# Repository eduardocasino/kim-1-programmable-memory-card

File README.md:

# KIM-1 Programmable Memory Board for the MTU Backplane

## **WARNINGS**

**THIS IS A WORK IN PROGRESS AND MAY CONTAIN ERRORS. USE AT YOUR OWN RISK!!!**

**Make sure to configure composite video output when connecting a composite monitor, and VGA output when using a VGA monitor. The video data and HSYNC pins are shared between both connectors, and if not properly configured, the signal MAY DAMAGE your monitor — especially older models.**

## About

This is a fully programmable RAM/ROM expansion board for the KIM-1. Two hardware versions are available which use exactly the same firmware and tools:

* One for MTU backplanes, like the one in the original K-1005 card file, my [expansion card](https://github.com/eduardocasino/kim-1-mtu-expansion-card) or my [buffered motherboard](https://github.com/eduardocasino/kim-1-mtu-motherboard).
* One for the [PAL-2](https://www.tindie.com/products/kim1/pal-2-a-mos-6502-powered-computer-kit/), a KIM-1 clone by Liu GN. **IMPORTANT: Read the hardware specific notes for the PAL-2**.

There is also [an adapter](https://github.com/eduardocasino/kim-1-programmable-memory-card/tree/main/hardware/pal-2-kim-adapter) for connecting the PAL-2 version directly to the KIM-1 expansion connector. This is the best option if you don't have/need/want an MTU backplane.

It uses a Raspberry Pi Pico W to emulate the 64K RAM/ROM memory map, and has some cool features:

* Can emulate RAM and/or ROM at any address of the KIM-1 memory map and with byte granularity so you can individually enable, disable, mark as RW or RO each and every byte of the 64K address space. It can also take over the KIM-1 system RAM and ROM, so it can be used as a diagnostic tool or to relive a KIM-1 with dead RAM.
* A default memory map and data are stored in the Pico flash memory and it is available at boot time.
* Runs a configuration web server with a RESTish API so you can configure and read or write all or any part of memory contents over Wifi and on the fly.
* The board is powered by the KIM-1, but it can also be dual powered by the KIM-1 and the USB port. This is useful, for example, if you are developing a boot ROM: you can power off the KIM, modify the boot program over wifi and turn it on again to test your changes.
* It emulates an [MTU K-1008 Visable Memory Card](https://github.com/eduardocasino/k-1008-visable-memory-card-replica). It can be mapped to the same addresses as the real one (and change that mapping while running) and gives configurable composite NTSC or PAL output through the RCA connector or VGA output through the DB-15 one. Simultaneous composite and VGA output is not possible.
* Emulates an [K-1013 floppy disk controller](http://retro.hansotten.nl/uploads/mtu/MTU%20K-1013%20manual.pdf) with up to four disks, reading and writing to disk images into the SD card (Still in beta)

A config utility, memcfg, is provided to setup the board and facilitate the communication with the REST API. This is an overview of its functionality. Please see the [README.md file](https://github.com/eduardocasino/kim-1-programmable-memory-card/tree/main/tools) for detailed usage instructions:

* Generate configuration files ready to be flashed into the Pico: WiFi parameters, video format and default memory map and contents.
* Get or modify the memory map.
* Read memory contents and generate output in different formats: hexdump, Intel hex, binary, prg and raw. The raw format is how the Pico stores the memory map. Each memory address contains a 16 bit integer. The least significant byte is the content and the most significant one is a bitmap that indicates if the memory is enabled or disabled and writeable or read-only.
* Write memory contents from file or command line. The file formats supported are Intel hex, binary, prg and raw. Also, binary and raw data can be specified as a string from the command line.
* Modify the base address for the K-1008 emulation
* Manages disk images

### [KIM-1 version](https://github.com/eduardocasino/kim-1-programmable-memory-card/tree/main/hardware/kim-1-mtu)
### [PAL-2 version](https://github.com/eduardocasino/kim-1-programmable-memory-card/tree/main/hardware/pal-2)
### [KIM-1 adapter for the PAL-2 version](https://github.com/eduardocasino/kim-1-programmable-memory-card/tree/main/hardware/pal-2-kim-adapter)
### [Firmware](https://github.com/eduardocasino/kim-1-programmable-memory-card/tree/main/firmware)
### [Tools (memcfg)](https://github.com/eduardocasino/kim-1-programmable-memory-card/tree/main/tools)

***NOTE***: This is a picture of a KIM-1 version prototype. The bodges are not needed in the current design.

## Licensing

This is a personal project that I am sharing in case it is of interest to any retrocomputing enthusiast and all the information in this repository is provided "as is", without warranty of any kind. I am not liable for any damages that may occur, whether it be to individuals, objects, KIM-1 computers, kittens or any other pets. **It should also be noted that everything in this repository is a work in progress, may have not been thoroughly tested and may contain errors, therefore anyone who chooses to use it does so at their own risk**.

This work is licensed under a [Creative Commons Attribution-ShareAlike 4.0 International License](http://creativecommons.org/licenses/by-sa/4.0/).

See the LICENSE.md file for details.

## Acknowledgements

* Richard Hulme for his [PicoROM implementation](https://github.com/rhulme/picoROM_pio).
* Jan Cumps on [how to reserve a flash memory block for persistent storage](https://community.element14.com/products/raspberry-pi/b/blog/posts/raspberry-pico-c-sdk-reserve-a-flash-memory-block-for-persistent-storage).
* Jeremy P Bentham for his [PicoWi library](http://iosoft.blog/picowi)
* Alan Reed for his [composite video output implementation](https://github.com/alanpreed/pico-composite-video).
* Hunter Adams for his [VGA implementation](https://github.com/vha3/Hunter-Adams-RP2040-Demos)
* Luciano Veronese for the BOM and component placement files for the KIM-1 version.

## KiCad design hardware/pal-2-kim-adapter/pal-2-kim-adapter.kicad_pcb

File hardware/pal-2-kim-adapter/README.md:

# PAL-2 version to KIM-1 adapter

## DECEN signal

As well as for the PAL, the DECEN pin must be connected to pin K in the Application connector. You can do this using a clip probe.

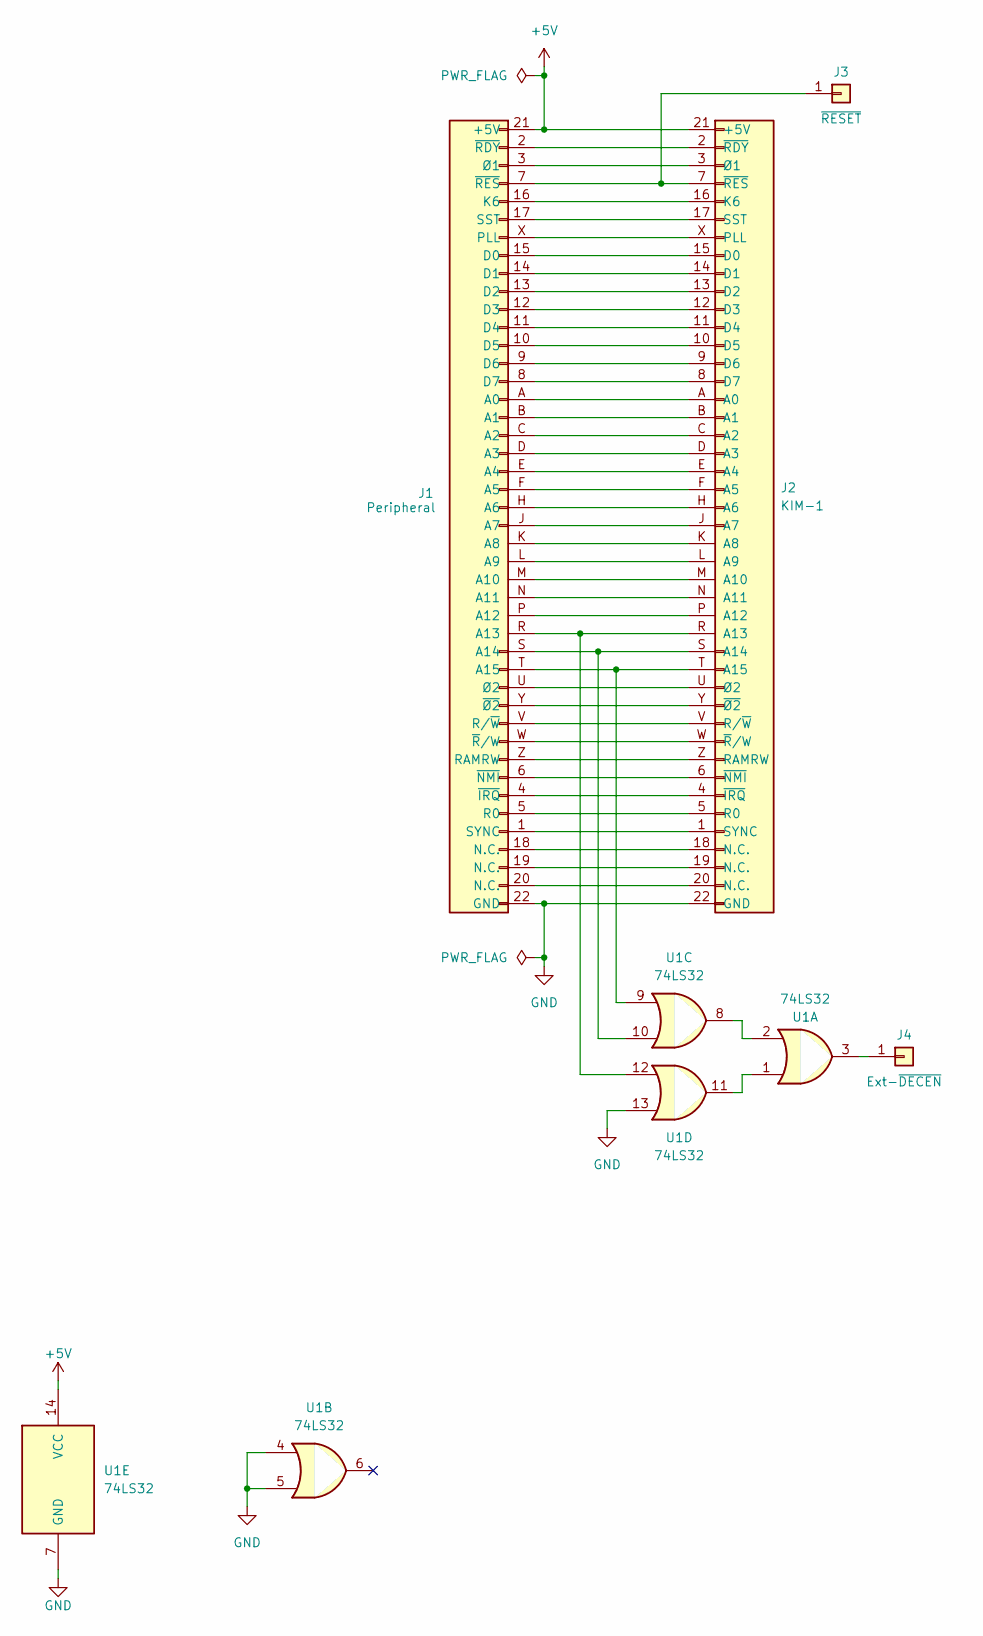
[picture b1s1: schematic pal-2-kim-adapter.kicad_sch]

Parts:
J1: Peripheral; PinSocket_2x22_P2.54mm_Horizontal
J2: KIM-1; KIM_EDGE
J3: ~{RESET}; PinHeader_1x01_P2.54mm_Horizontal
J4: Ext-~{DECEN}; PinHeader_1x01_P2.54mm_Vertical
U1: 74LS32; DIP-14_W7.62mm

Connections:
+5V: J1.21 (+5V), J2.21 (+5V), U1.14 (VCC)
GND: J1.22 (GND), J2.22 (GND), U1.4, U1.5, U1.7 (GND), U1.13
unnamed: J1.A (A0), J2.A (A0)
unnamed: J1.B (A1), J2.B (A1)
unnamed: J1.C (A2), J2.C (A2)
unnamed: J1.D (A3), J2.D (A3)
unnamed: J1.E (A4), J2.E (A4)
unnamed: J1.F (A5), J2.F (A5)
unnamed: J1.H (A6), J2.H (A6)
unnamed: J1.J (A7), J2.J (A7)
unnamed: J1.K (A8), J2.K (A8)
unnamed: J1.L (A9), J2.L (A9)
unnamed: J1.M (A10), J2.M (A10)
unnamed: J1.N (A11), J2.N (A11)
unnamed: J1.P (A12), J2.P (A12)
unnamed: J1.R (A13), J2.R (A13), U1.12
unnamed: J1.S (A14), J2.S (A14), U1.10
unnamed: J1.T (A15), J2.T (A15), U1.9
unnamed: J1.15 (D0), J2.15 (D0)
unnamed: J1.14 (D1), J2.14 (D1)
unnamed: J1.13 (D2), J2.13 (D2)
unnamed: J1.12 (D3), J2.12 (D3)
unnamed: J1.11 (D4), J2.11 (D4)
unnamed: J1.10 (D5), J2.10 (D5)
unnamed: J1.9 (D6), J2.9 (D6)
unnamed: J1.8 (D7), J2.8 (D7)
unnamed: J1.16 (K6), J2.16 (K6)
unnamed: J1.18 (N.C.), J2.18 (N.C.)
unnamed: J1.19 (N.C.), J2.19 (N.C.)
unnamed: J1.20 (N.C.), J2.20 (N.C.)
unnamed: J1.X (PLL), J2.X (PLL)
unnamed: J1.5 (R0), J2.5 (R0)
unnamed: J1.Z (RAMRW), J2.Z (RAMRW)
unnamed: J1.V (R/~W), J2.V (R/~W)
unnamed: J1.17 (SST), J2.17 (SST)
unnamed: J1.1 (SYNC), J2.1 (SYNC)
unnamed: J1.4 (~IRQ), J2.4 (~IRQ)
unnamed: J1.6 (~NMI), J2.6 (~NMI)
unnamed: J1.2 (~RDY), J2.2 (~RDY)
unnamed: J1.7 (~RES), J2.7 (~RES), J3.1
unnamed: J1.W (~R/W), J2.W (~R/W)
unnamed: J1.Y (~Ø2), J2.Y (~Ø2)
unnamed: J1.3 (Ø1), J2.3 (Ø1)
unnamed: J1.U (Ø2), J2.U (Ø2)
unnamed: J4.1, U1.3
unnamed: U1.1, U1.11
unnamed: U1.2, U1.8

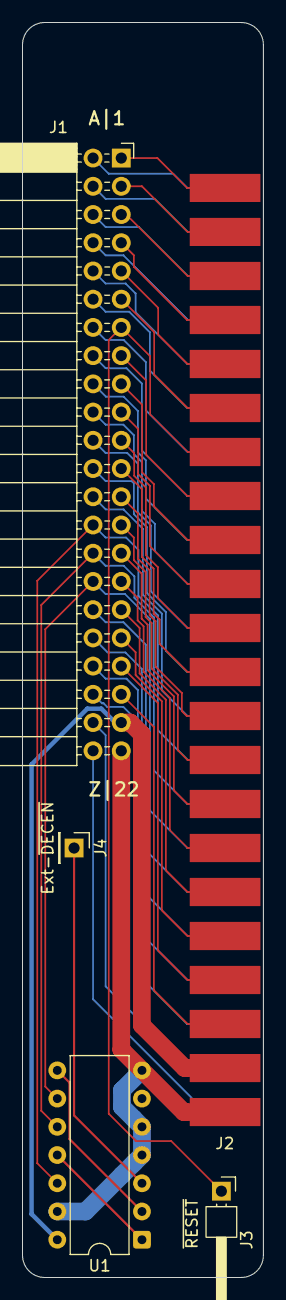
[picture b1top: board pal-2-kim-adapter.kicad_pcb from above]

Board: 2 copper layers, 21.7 x 112.9 mm, 5 parts (0 on the bottom side), 47 nets.

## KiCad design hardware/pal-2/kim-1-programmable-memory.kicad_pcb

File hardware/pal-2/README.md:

# Notes for the PAL-2 version

## DECEN signal

The DECEN pin must be connected to pin K in the Application connector. You can do this using a clip probe as shown in the picture below:

## PAL-2 mod

### **WARNING**

**THIS MOD MAY DAMAGE YOUR PAL-2 IF PERFORMED INCORRECTLY. DO IT AT YOUR OWN RISK!!!**

The PAL-2 behaves differently from the KIM-1 when the #DECEN signal goes high.

On the KIM-1, this signal disables all internal address decoding, allowing an expansion card to take over. However, on the PAL-2, the signal is wire-ORed with the 8K0 enable output of the first decoder, so it effectively has no impact.

To enable expansion card functionality, a simple modification must be performed on the PAL-2:

* Cut the trace that connects pin K of the Application connector to pin 12 of U6, and the trace connecting pin 12 of U8 to ground.
* Solder a wire from pin K of the Application connector to pin 12 of U8.
* Solder a 3.9kΩ resistor from pin 12 of U8 to any ground point on the board.

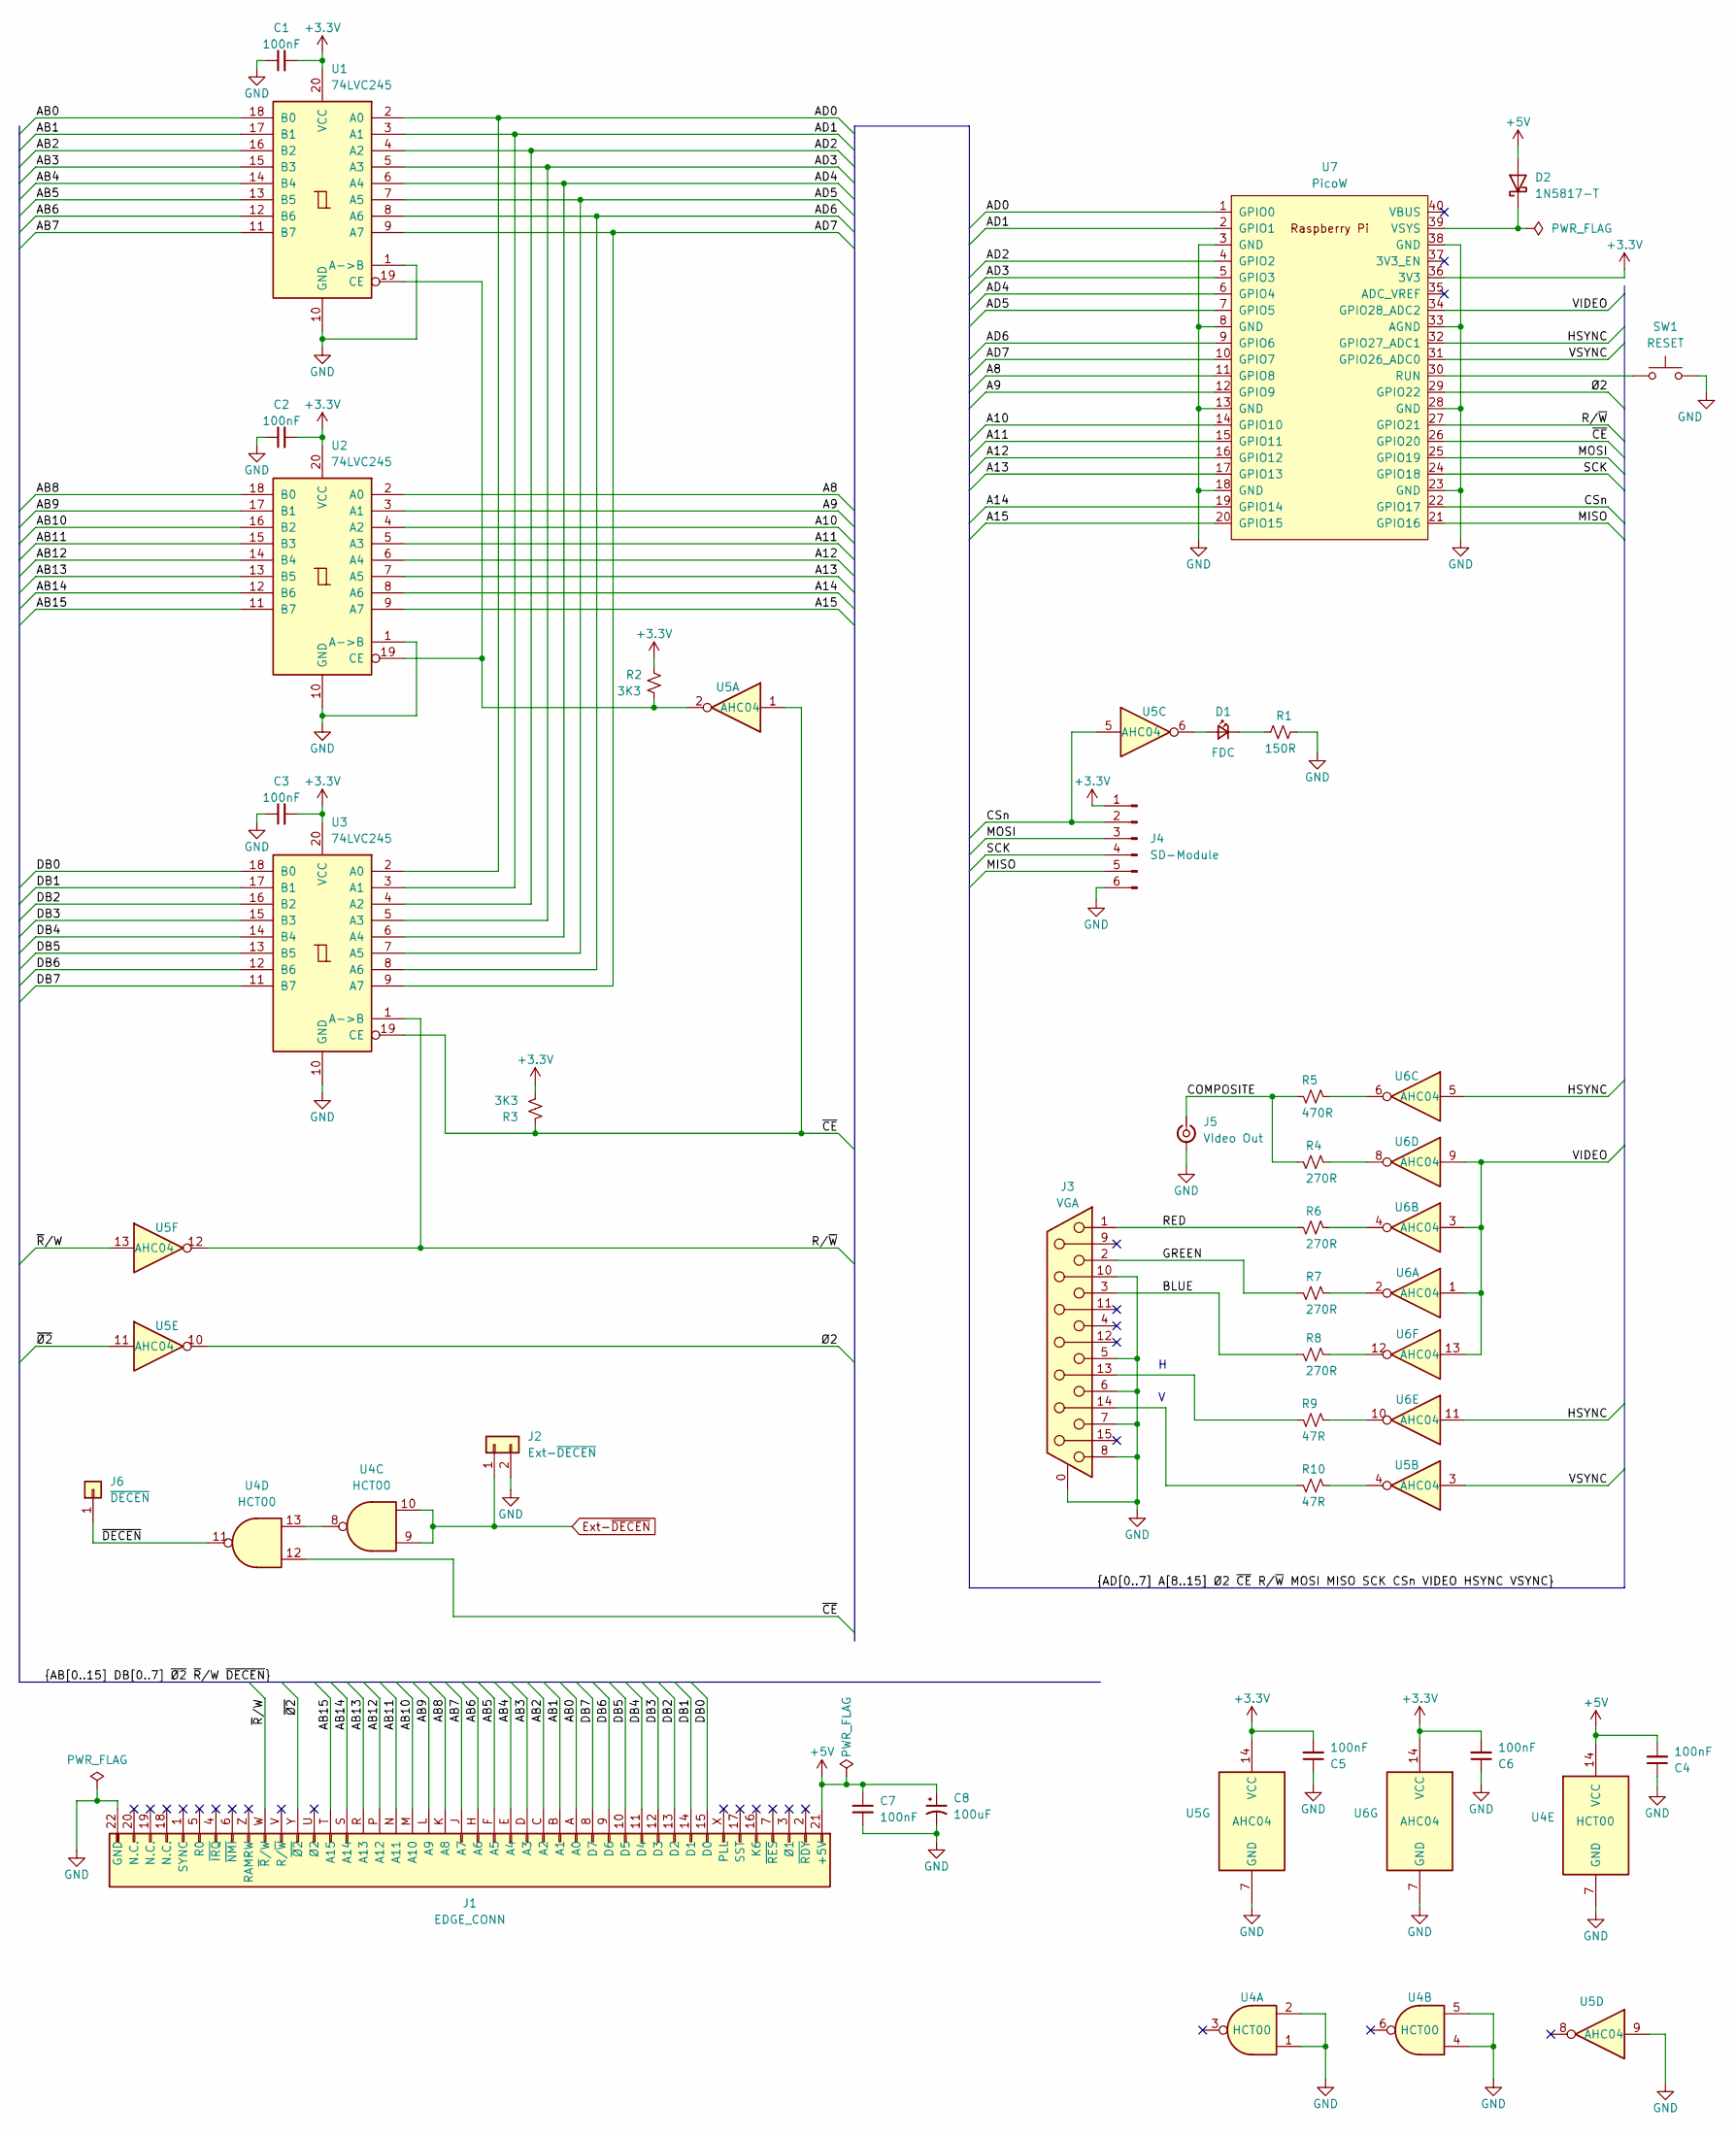
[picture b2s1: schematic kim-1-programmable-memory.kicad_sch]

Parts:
C1: 100nF; C_Disc_D5.0mm_W2.5mm_P5.00mm; MPN C14663
C2, C3, C4, C5, C6: 100nF; C_Disc_D5.0mm_W2.5mm_P5.00mm; LCSC C14663
C7: 100nF; C_Disc_D5.0mm_W2.5mm_P5.00mm; LCSC C28233
C8: 100uF; CP_Axial_L10.0mm_D6.0mm_P15.00mm_Horizontal; LCSC C178540
D1: FDC; LED_D3.0mm_Clear; LCSC C2286
D2: 1N5817-T; D_DO-41_SOD81_P7.62mm_Horizontal
J1: EDGE_CONN; PinHeader_2x22_P2.54mm_Horizontal
J2: Ext-~{DECEN}; PinHeader_1x02_P2.54mm_Vertical
J3: VGA; DSUB-15-HD_Female_Horizontal_P2.29x1.98mm_EdgePinOffset3.03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; LCSC C711364
J4: SD-Module; SD_Module_Small
J5: VIdeo Out; CUI_RCJ-014
J6: ~{DECEN}; PinHeader_1x01_P2.54mm_Vertical
R1: 150R; R_Axial_DIN0207_L6.3mm_D2.5mm_P7.62mm_Horizontal; LCSC C22775
R2, R3: 3K3; R_Axial_DIN0207_L6.3mm_D2.5mm_P7.62mm_Horizontal; LCSC C22978
R4, R6, R7, R8: 270R; R_Axial_DIN0207_L6.3mm_D2.5mm_P7.62mm_Horizontal; LCSC C22966
R5: 470R; R_Axial_DIN0207_L6.3mm_D2.5mm_P7.62mm_Horizontal; LCSC C23179
R9, R10: 47R; R_Axial_DIN0207_L6.3mm_D2.5mm_P7.62mm_Horizontal; LCSC C23182
SW1: RESET; SW_PUSH_6mm; LCSC C455245
U1, U2, U3: 74LVC245; DIP-20_W7.62mm_Socket; LCSC C571201
U4: HCT00; DIP-14_W7.62mm_Socket
U5, U6: AHC04; DIP-14_W7.62mm_Socket; LCSC C485074
U7: PicoW; RPi_PicoW_SMD_TH

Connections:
+3.3V: C1.2, C2.2, C3.2, C5.2, C6.2, J4.1, R2.1, R3.2, U1.20 (VCC), U2.20 (VCC), U3.20 (VCC), U5.14 (VCC), U6.14 (VCC), U7.36 (3V3)
+5V: C4.2, C7.1, C8.1, D2.2 (A), J1.21 (+5V), U4.14 (VCC)
/A8: U2.2 (A0), U7.11 (GPIO8)
/A9: U2.3 (A1), U7.12 (GPIO9)
/A10: U2.4 (A2), U7.14 (GPIO10)
/A11: U2.5 (A3), U7.15 (GPIO11)
/A12: U2.6 (A4), U7.16 (GPIO12)
/A13: U2.7 (A5), U7.17 (GPIO13)
/A14: U2.8 (A6), U7.19 (GPIO14)
/A15: U2.9 (A7), U7.20 (GPIO15)
/AB0: J1.A (A0), U1.18 (B0)
/AB1: J1.B (A1), U1.17 (B1)
/AB2: J1.C (A2), U1.16 (B2)
/AB3: J1.D (A3), U1.15 (B3)
/AB4: J1.E (A4), U1.14 (B4)
/AB5: J1.F (A5), U1.13 (B5)
/AB6: J1.H (A6), U1.12 (B6)
/AB7: J1.J (A7), U1.11 (B7)
/AB8: J1.K (A8), U2.18 (B0)
/AB9: J1.L (A9), U2.17 (B1)
/AB10: J1.M (A10), U2.16 (B2)
/AB11: J1.N (A11), U2.15 (B3)
/AB12: J1.P (A12), U2.14 (B4)
/AB13: J1.R (A13), U2.13 (B5)
/AB14: J1.S (A14), U2.12 (B6)
/AB15: J1.T (A15), U2.11 (B7)
/AD0: U1.2 (A0), U3.2 (A0), U7.1 (GPIO0)
/AD1: U1.3 (A1), U3.3 (A1), U7.2 (GPIO1)
/AD2: U1.4 (A2), U3.4 (A2), U7.4 (GPIO2)
/AD3: U1.5 (A3), U3.5 (A3), U7.5 (GPIO3)
/AD4: U1.6 (A4), U3.6 (A4), U7.6 (GPIO4)
/AD5: U1.7 (A5), U3.7 (A5), U7.7 (GPIO5)
/AD6: U1.8 (A6), U3.8 (A6), U7.9 (GPIO6)
/AD7: U1.9 (A7), U3.9 (A7), U7.10 (GPIO7)
/BLUE: J3.3, R8.1
/COMPOSITE: J5.1 (In), R4.1, R5.1
/CSn: J4.2, U5.5, U7.22 (GPIO17)
/DB0: J1.15 (D0), U3.18 (B0)
/DB1: J1.14 (D1), U3.17 (B1)
/DB2: J1.13 (D2), U3.16 (B2)
/DB3: J1.12 (D3), U3.15 (B3)
/DB4: J1.11 (D4), U3.14 (B4)
/DB5: J1.10 (D5), U3.13 (B5)
/DB6: J1.9 (D6), U3.12 (B6)
/DB7: J1.8 (D7), U3.11 (B7)
/GREEN: J3.2, R7.1
/HSYNC: U6.5, U6.11, U7.32 (GPIO27_ADC1)
/MISO: J4.5, U7.21 (GPIO16)
/MOSI: J4.3, U7.25 (GPIO19)
/RED: J3.1, R6.1
/R/~W: U3.1 (A->B), U5.12, U7.27 (GPIO21)
/SCK: J4.4, U7.24 (GPIO18)
/VIDEO: U6.1, U6.3, U6.9, U6.13, U7.34 (GPIO28_ADC2)
/VSYNC: U5.3, U7.31 (GPIO26_ADC0)
/~CE: R3.1, U3.19 (CE), U4.12, U5.1, U7.26 (GPIO20)
/~DECEN: J6.1, U4.11
/~R/W: J1.W (~R/W), U5.13
/~Ø2: J1.Y (~Ø2), U5.11
/Ø2: U5.10, U7.29 (GPIO22)
Ext-~DECEN: J2.1, U4.9, U4.10
GND: C1.1, C2.1, C3.1, C4.1, C5.1, C6.1, C7.2, C8.2, J1.22 (GND), J2.2, J3.0 (PAD), J3.5, J3.6, J3.7, J3.8, J3.10, J4.6, J5.2 (Ext), R1.1, SW1.2, U1.1 (A->B), U1.10 (GND), U2.1 (A->B), U2.10 (GND), U3.10 (GND), U4.1, U4.2, U4.4, U4.5, U4.7 (GND), U5.7 (GND), U5.9, U6.7 (GND), U7.3 (GND), U7.8 (GND), U7.13 (GND), U7.18 (GND), U7.23 (GND), U7.28 (GND), U7.33 (AGND), U7.38 (GND)
unnamed: D1.2 (A), U5.6
unnamed: D1.1 (K), R1.2
unnamed: D2.1 (K), U7.39 (VSYS)
unnamed: J3.13, R9.1
unnamed: J3.14, R10.1
unnamed: R4.2, U6.8
unnamed: R5.2, U6.6
unnamed: R6.2, U6.4
unnamed: R7.2, U6.2
unnamed: R8.2, U6.12
unnamed: R9.2, U6.10
unnamed: R10.2, U5.4
unnamed: R2.2, U1.19 (CE), U2.19 (CE), U5.2
unnamed: U4.8, U4.13
unnamed: SW1.1, U7.30 (RUN)

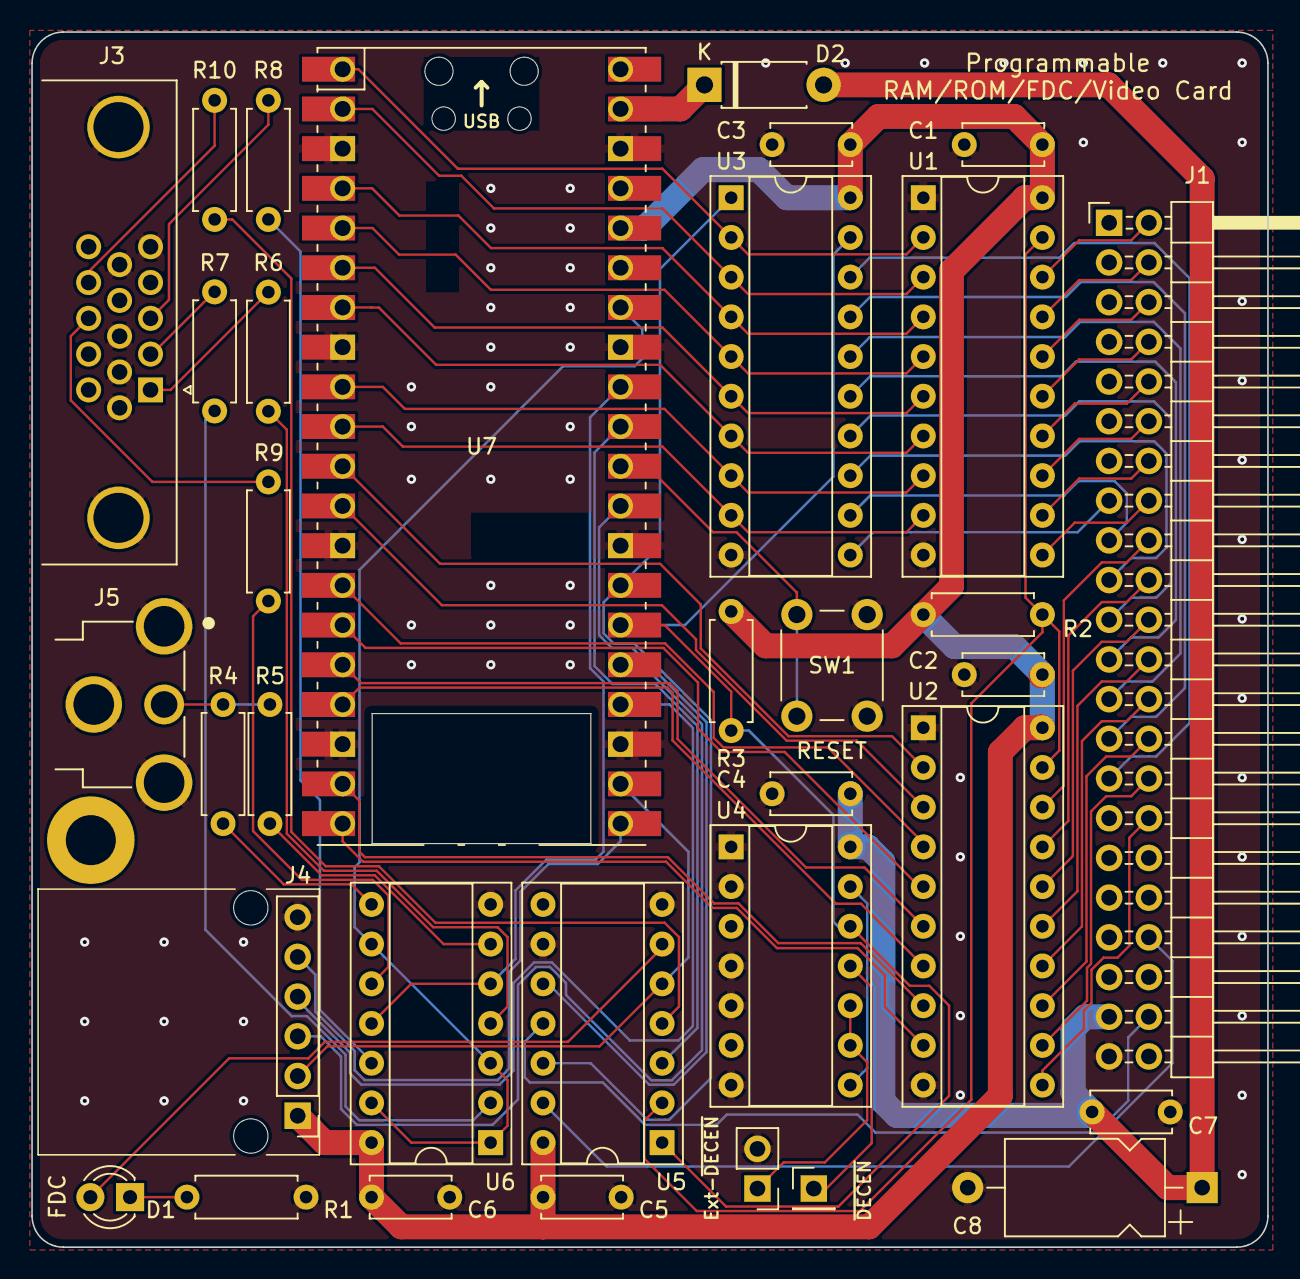
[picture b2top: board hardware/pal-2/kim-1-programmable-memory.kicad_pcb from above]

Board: 2 copper layers, 79.1 x 77.7 mm, 34 parts (0 on the bottom side), 76 nets.

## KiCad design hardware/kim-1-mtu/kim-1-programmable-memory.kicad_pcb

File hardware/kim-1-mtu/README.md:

# Notes for the KIM-1 MTU version

## BOM and component placement list

Thanks to Luciano Veronese, we now have a [BOM](https://github.com/eduardocasino/kim-1-programmable-memory-card/tree/main/hardware/kim-1-mtu/docs/bom.csv) and a [component placement list](https://github.com/eduardocasino/kim-1-programmable-memory-card/tree/main/hardware/kim-1-mtu/docs/positions.csv) for use with JLCPCB. They are under the [docs folder](https://github.com/eduardocasino/kim-1-programmable-memory-card/tree/main/hardware/kim-1-mtu/docs/).

Only the coaxial connector and the PicoW are missing, but they are very easy to solder.

Picture by Luciano Veronese

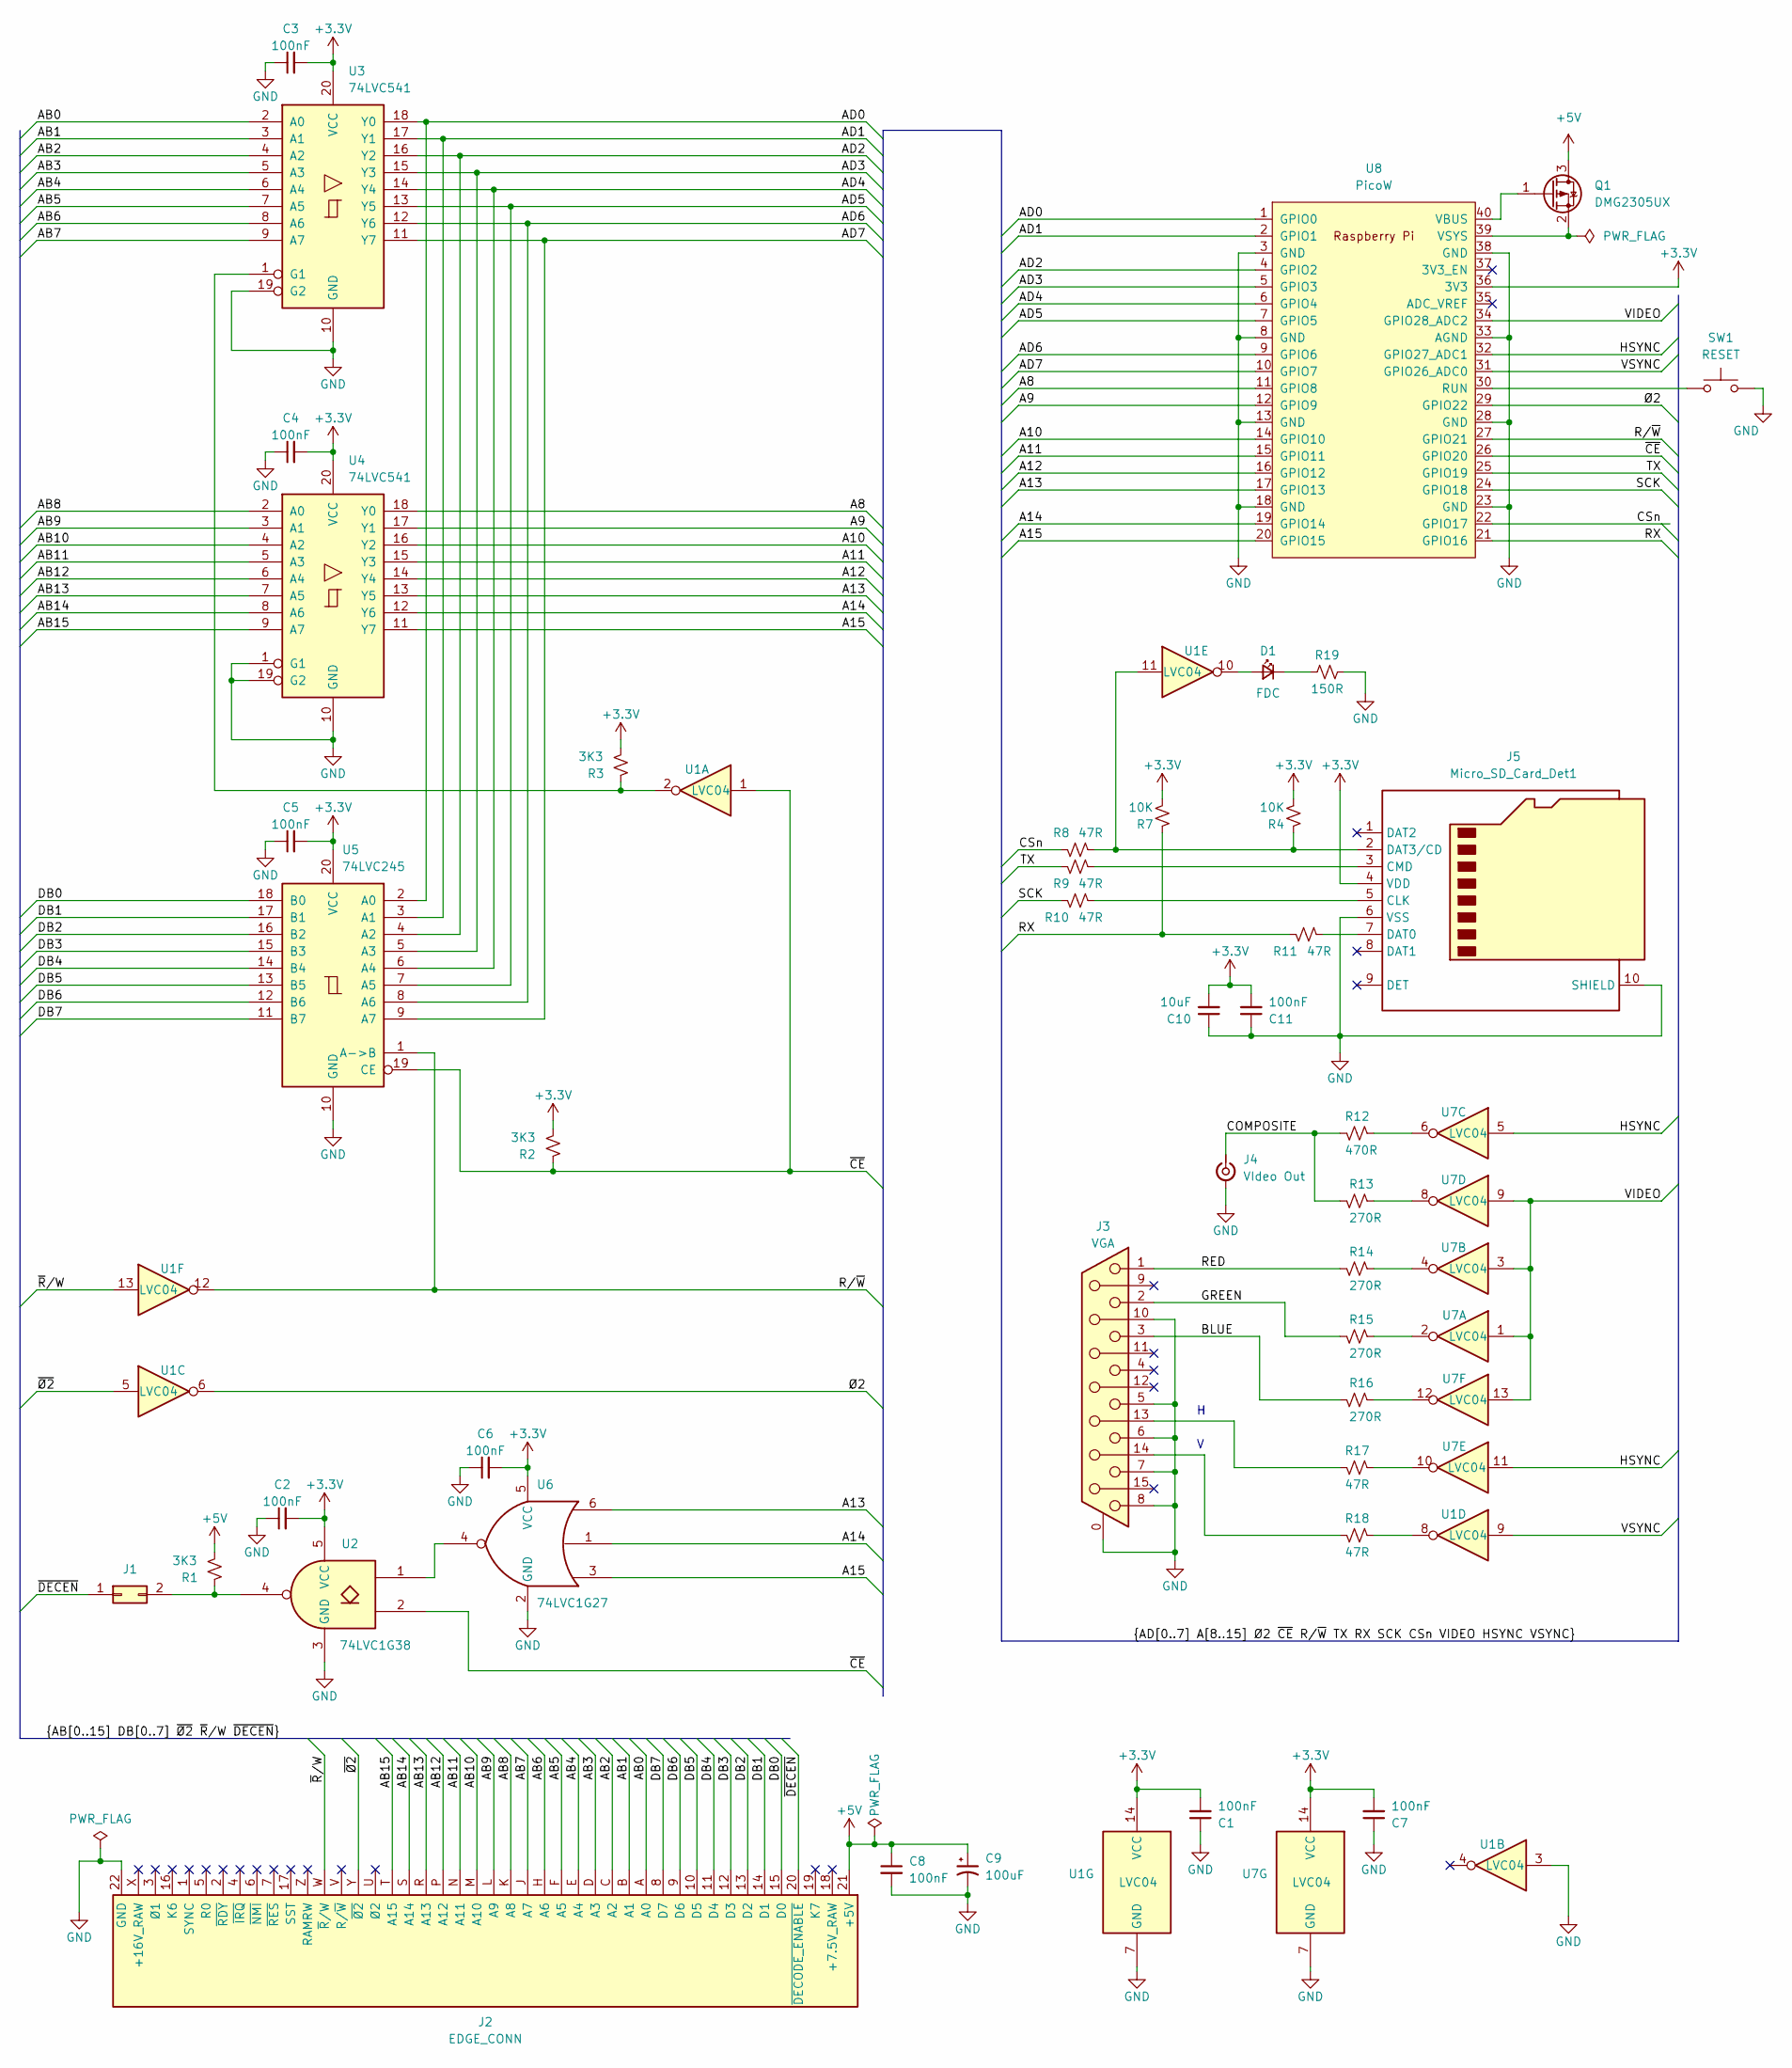
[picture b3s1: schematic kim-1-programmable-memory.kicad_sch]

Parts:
C1, C2, C4, C5, C6, C7, C11: 100nF; C_0603_1608Metric_Pad1.08x0.95mm_HandSolder; LCSC C14663
C3: 100nF; C_0603_1608Metric_Pad1.08x0.95mm_HandSolder; MPN C14663
C8: 100nF; C_0805_2012Metric_Pad1.18x1.45mm_HandSolder; LCSC C28233
C9: 100uF; CP_Elec_6.3x5.9; LCSC C178540
C10: 10uF; C_0603_1608Metric_Pad1.08x0.95mm_HandSolder; LCSC C96446
D1: FDC; LED_0603_1608Metric_Pad1.05x0.95mm_HandSolder; LCSC C2286
J1: Conn_02x01; PinHeader_1x02_P2.54mm_Vertical
J2: EDGE_CONN
J3: VGA; DSUB-15-HD_Female_Horizontal_P2.29x1.98mm_EdgePinOffset3.03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; LCSC C711364
J4: VIdeo Out; CUI_RCJ-014
J5: Micro_SD_Card_Det1; SD_Card_Holder_SMD_WQ21801-B2180-7F; LCSC C266620
Q1: DMG2305UX; SOT-23; LCSC C150470
R1, R2, R3: 3K3; R_0603_1608Metric_Pad0.98x0.95mm_HandSolder; LCSC C22978
R4, R7: 10K; R_0603_1608Metric_Pad0.98x0.95mm_HandSolder; LCSC C25804
R8, R9, R10, R11, R17, R18: 47R; R_0603_1608Metric_Pad0.98x0.95mm_HandSolder; LCSC C23182
R12: 470R; R_0603_1608Metric_Pad0.98x0.95mm_HandSolder; LCSC C23179
R13, R14, R15, R16: 270R; R_0603_1608Metric_Pad0.98x0.95mm_HandSolder; LCSC C22966
R19: 150R; R_0603_1608Metric_Pad0.98x0.95mm_HandSolder; LCSC C22775
SW1: RESET; SW_SPST_TL3305A; LCSC C455245
U1, U7: LVC04; SOIC-14_3.9x8.7mm_P1.27mm; LCSC C485074
U2: 74LVC1G38; SOT-23-5_HandSoldering; LCSC C2867613
U3, U4: 74LVC541; SOIC-20W_7.5x12.8mm_P1.27mm; LCSC C2652110
U5: 74LVC245; SOIC-20W_7.5x12.8mm_P1.27mm; LCSC C571201
U6: 74LVC1G27; SOT-23-6_Handsoldering; LCSC C128410
U8: PicoW; RPi_PicoW_SMD

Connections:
+3.3V: C1.2, C2.2, C3.2, C4.2, C5.2, C6.2, C7.2, C10.2, C11.2, J5.4 (VDD), R2.2, R3.2, R4.2, R7.2, U1.14 (VCC), U2.5 (VCC), U3.20 (VCC), U4.20 (VCC), U5.20 (VCC), U6.5 (VCC), U7.14 (VCC), U8.36 (3V3)
+5V: C8.1, C9.1, J2.21 (+5V), Q1.3 (D), R1.2
/A8: U4.18 (Y0), U8.11 (GPIO8)
/A9: U4.17 (Y1), U8.12 (GPIO9)
/A10: U4.16 (Y2), U8.14 (GPIO10)
/A11: U4.15 (Y3), U8.15 (GPIO11)
/A12: U4.14 (Y4), U8.16 (GPIO12)
/A13: U4.13 (Y5), U6.6, U8.17 (GPIO13)
/A14: U4.12 (Y6), U6.1, U8.19 (GPIO14)
/A15: U4.11 (Y7), U6.3, U8.20 (GPIO15)
/AB0: J2.A (A0), U3.2 (A0)
/AB1: J2.B (A1), U3.3 (A1)
/AB2: J2.C (A2), U3.4 (A2)
/AB3: J2.D (A3), U3.5 (A3)
/AB4: J2.E (A4), U3.6 (A4)
/AB5: J2.F (A5), U3.7 (A5)
/AB6: J2.H (A6), U3.8 (A6)
/AB7: J2.J (A7), U3.9 (A7)
/AB8: J2.K (A8), U4.2 (A0)
/AB9: J2.L (A9), U4.3 (A1)
/AB10: J2.M (A10), U4.4 (A2)
/AB11: J2.N (A11), U4.5 (A3)
/AB12: J2.P (A12), U4.6 (A4)
/AB13: J2.R (A13), U4.7 (A5)
/AB14: J2.S (A14), U4.8 (A6)
/AB15: J2.T (A15), U4.9 (A7)
/AD0: U3.18 (Y0), U5.2 (A0), U8.1 (GPIO0)
/AD1: U3.17 (Y1), U5.3 (A1), U8.2 (GPIO1)
/AD2: U3.16 (Y2), U5.4 (A2), U8.4 (GPIO2)
/AD3: U3.15 (Y3), U5.5 (A3), U8.5 (GPIO3)
/AD4: U3.14 (Y4), U5.6 (A4), U8.6 (GPIO4)
/AD5: U3.13 (Y5), U5.7 (A5), U8.7 (GPIO5)
/AD6: U3.12 (Y6), U5.8 (A6), U8.9 (GPIO6)
/AD7: U3.11 (Y7), U5.9 (A7), U8.10 (GPIO7)
/BLUE: J3.3, R16.1
/COMPOSITE: J4.1 (In), R12.1, R13.1
/CSn: R8.1, U8.22 (GPIO17)
/DB0: J2.15 (D0), U5.18 (B0)
/DB1: J2.14 (D1), U5.17 (B1)
/DB2: J2.13 (D2), U5.16 (B2)
/DB3: J2.12 (D3), U5.15 (B3)
/DB4: J2.11 (D4), U5.14 (B4)
/DB5: J2.10 (D5), U5.13 (B5)
/DB6: J2.9 (D6), U5.12 (B6)
/DB7: J2.8 (D7), U5.11 (B7)
/GREEN: J3.2, R15.1
/HSYNC: U7.5, U7.11, U8.32 (GPIO27_ADC1)
/RED: J3.1, R14.1
/RX: R7.1, R11.1, U8.21 (GPIO16)
/R/~W: U1.12, U5.1 (A->B), U8.27 (GPIO21)
/SCK: R10.1, U8.24 (GPIO18)
/TX: R9.1, U8.25 (GPIO19)
/VIDEO: U7.1, U7.3, U7.9, U7.13, U8.34 (GPIO28_ADC2)
/VSYNC: U1.9, U8.31 (GPIO26_ADC0)
/~CE: R2.1, U1.1, U2.2, U5.19 (CE), U8.26 (GPIO20)
/~DECEN: J1.1, J2.20 (~DECODE_ENABLE)
/~R/W: J2.W (~R/W), U1.13
/~Ø2: J2.Y (~Ø2), U1.5
/Ø2: U1.6, U8.29 (GPIO22)
GND: C1.1, C2.1, C3.1, C4.1, C5.1, C6.1, C7.1, C8.2, C9.2, C10.1, C11.1, J2.22 (GND), J3.0 (PAD), J3.5, J3.6, J3.7, J3.8, J3.10, J4.2 (Ext), J5.6 (VSS), J5.10 (SHIELD), R19.1, SW1.2, U1.3, U1.7 (GND), U2.3 (GND), U3.10 (GND), U3.19 (G2), U4.1 (G1), U4.10 (GND), U4.19 (G2), U5.10 (GND), U6.2 (GND), U7.7 (GND), U8.3 (GND), U8.8 (GND), U8.13 (GND), U8.18 (GND), U8.23 (GND), U8.28 (GND), U8.33 (AGND), U8.38 (GND)
unnamed: D1.2 (A), U1.10
unnamed: D1.1 (K), R19.2
unnamed: J1.2, R1.1, U2.4
unnamed: J3.13, R17.1
unnamed: J3.14, R18.1
unnamed: J5.5 (CLK), R10.2
unnamed: J5.3 (CMD), R9.2
unnamed: J5.7 (DAT0), R11.2
unnamed: J5.2 (DAT3/CD), R4.1, R8.2, U1.11
unnamed: Q1.1 (G), U8.40 (VBUS)
unnamed: Q1.2 (S), U8.39 (VSYS)
unnamed: R12.2, U7.6
unnamed: R13.2, U7.8
unnamed: R14.2, U7.4
unnamed: R15.2, U7.2
unnamed: R16.2, U7.12
unnamed: R17.2, U7.10
unnamed: R18.2, U1.8
unnamed: U2.1, U6.4
unnamed: R3.1, U1.2, U3.1 (G1)
unnamed: SW1.1, U8.30 (RUN)

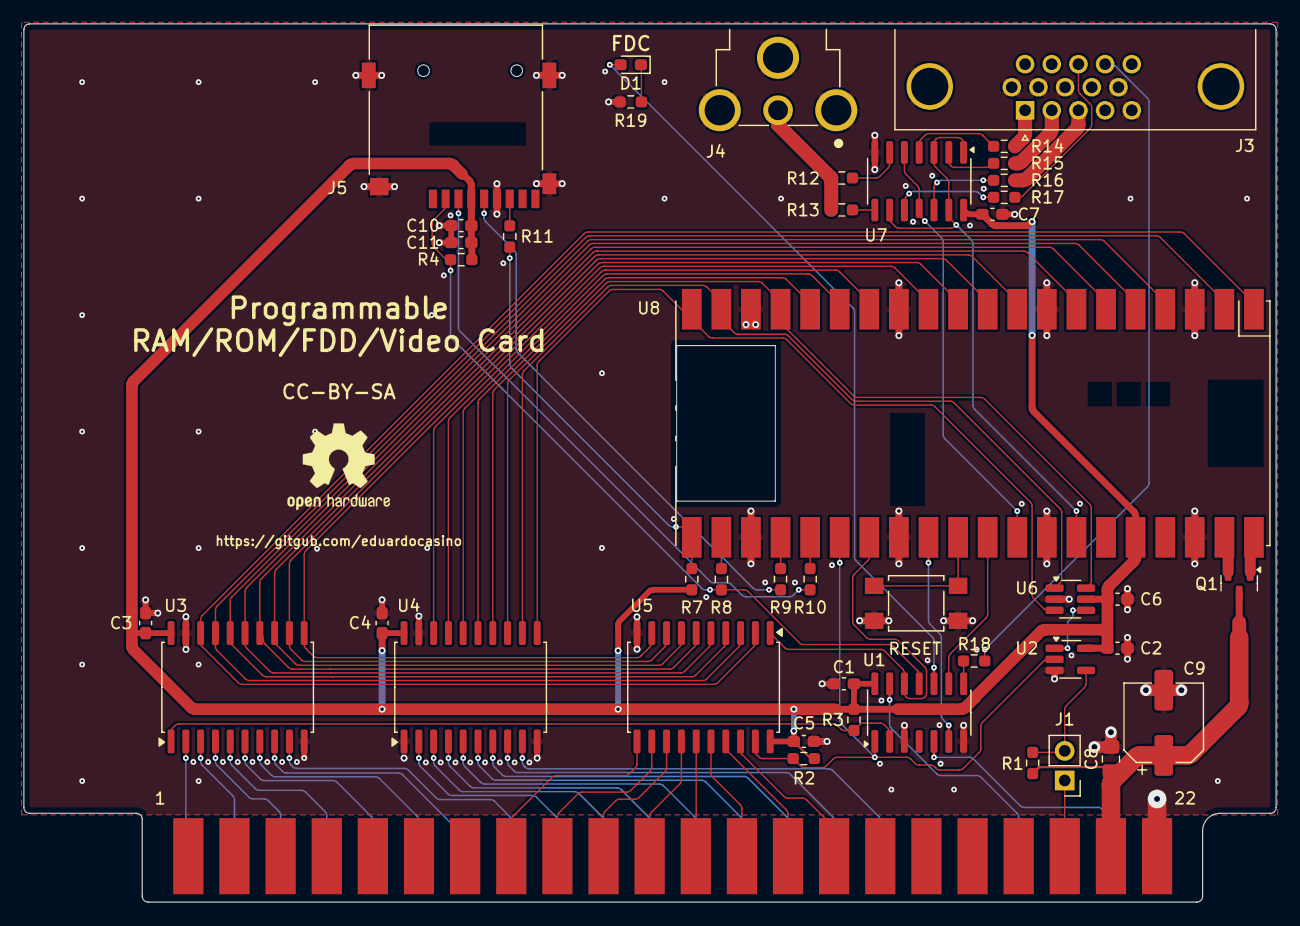
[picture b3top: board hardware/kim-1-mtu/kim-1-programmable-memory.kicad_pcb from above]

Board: 2 copper layers, 107.5 x 75.4 mm, 44 parts (0 on the bottom side), 81 nets.

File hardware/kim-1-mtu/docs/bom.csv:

Designator,Footprint,Quantity,Value,LCSC Part #
"C1, C11, C2, C3, C4, C5, C6, C7",0603,8,100nF,C14663
C10,0603,1,10uF,C96446
C8,0805,1,100nF,C28233
C9,CP_Elec_6.3x5.9,1,100uF,C178540
D1,0603,1,FDC,C2286
J3,DSUB-15-HD_Female_Horizontal_P2.29x1.98mm_EdgePinOffset3.03mm_Housed_MountingHolesOffset4.94mm,1,VGA,C711364
J5,SD_Card_Holder_SMD_WQ21801-B2180-7F,1,Micro_SD_Card_Det1,C266620
Q1,SOT-23,1,DMG2305UX,C150470
"R1, R2, R3",0603,3,3K3,C22978
"R10, R11, R17, R18, R8, R9",0603,6,47R,C23182
R12,0603,1,470R,C23179
"R13, R14, R15, R16",0603,4,270R,C22966
R19,0603,1,150R,C22775
"R4, R7",0603,2,10K,C25804
SW1,SW_SPST_TL3305A,1,RESET,C455245
"U1, U7",SOIC-14_3.9x8.7mm_P1.27mm,2,LVC04,C485074
U2,SOT-23-5_HandSoldering,1,74LVC1G38,C2867613
"U3, U4",SOIC-20W_7.5x12.8mm_P1.27mm,2,74LVC541,C2652110
U5,SOIC-20W_7.5x12.8mm_P1.27mm,1,74LVC245,C571201
U6,SOT-23-6_Handsoldering,1,74LVC1G27,C128410

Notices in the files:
README.md:
Licensing:
[(https://i.creativecommons.org/l/by-sa/4.0/88
CC BY-SA 4.0
hardware/kim-1-mtu/kim-1-programmable-memory.kicad_pcb:
CC-BY-SA
